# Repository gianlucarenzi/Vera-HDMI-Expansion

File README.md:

# VERA-HDMI-Expansion

<p align="center">
  An open-source HDMI expansion board for the <strong>VERA-MODULE-RBL</strong> video module.
</p>

---

## 📖 Overview

This project provides the complete design files for an HDMI expansion board specifically created for the **VERA-MODULE-RBL**. Its purpose is to convert the VERA module's native video signal into a standard HDMI output, allowing it to be easily connected to modern monitors and TVs.

The project was designed in KiCad, and all source files are included for viewing, modification, and manufacturing.

## ✨ Key Features

- 🔌 **Native HDMI Output:** Delivers a clean digital signal for maximum video quality.
- 🧩 **Compact Design:** Engineered to integrate seamlessly with the VERA-MODULE-RBL.
- ⚙️ **MS9288-Based:** Utilizes a dedicated chip for digital video to HDMI conversion.
- 📂 **Open Source:** All KiCad design files are freely available in this repository.

## 🛠️ How It Works

The board connects directly to the VERA-MODULE-RBL. The heart of the circuit is the **MS9288A/C** video converter chip, a specialized IC that receives digital video data from the VERA module, processes it, and encodes it into a TMDS (Transition-Minimized Differential Signaling) signal compatible with the HDMI standard.

This signal is then exposed via a standard HDMI connector, ready to be plugged into any modern display.

---

## 📚 Project Files & Documentation

### Schematic

The complete circuit schematic is available as a PDF for easy viewing.

- **[➡️ View Schematic (PDF)](VERA-HDMI-Expansion.pdf)**

### Bill of Materials (BOM)

An interactive HTML Bill of Materials (iBOM) is provided to simplify component identification and assembly.

- **[➡️ Open Interactive BOM](https://gianlucarenzi.github.io/Vera-HDMI-Expansion/BOM/ibom.html)**

### Mechanical Assembly

The board is mounted on the VERA-MODULE-RBL-XE with four 14 mm M3 standoffs and
eight M3x6 screws; J2 plugs into the J1 box header of the module.

- **[➡️ Mechanical BOM and stacking](Documentation/MECHANICAL-BOM.md)**
- 3D model of the stack: [`images/VERA-XE-HDMI-assembly.step`](images/VERA-XE-HDMI-assembly.step)

---

## 🏭 Manufacturing

This repository contains all the necessary files for board production, including:
- KiCad source files (`.kicad_pcb`, `.sch`).
- Python scripts (`generate_cpl.py`, `jlcpcb-check-bom.py`) to automate the generation of Component Placement Lists (CPL) and to verify the BOM against JLCPCB's library.
- Manufacturing outputs in the `production/` directory.

### Board Renders

<table align="center">
  <tr>
    <td align="center"><strong>Top View</strong></td>
    <td align="center"><strong>Bottom View</strong></td>
  </tr>
  <tr>
    <td></td>
    <td></td>
  </tr>
</table>

---

## 📜 License

This project is released under the terms specified in the [LICENSE](LICENSE) file.

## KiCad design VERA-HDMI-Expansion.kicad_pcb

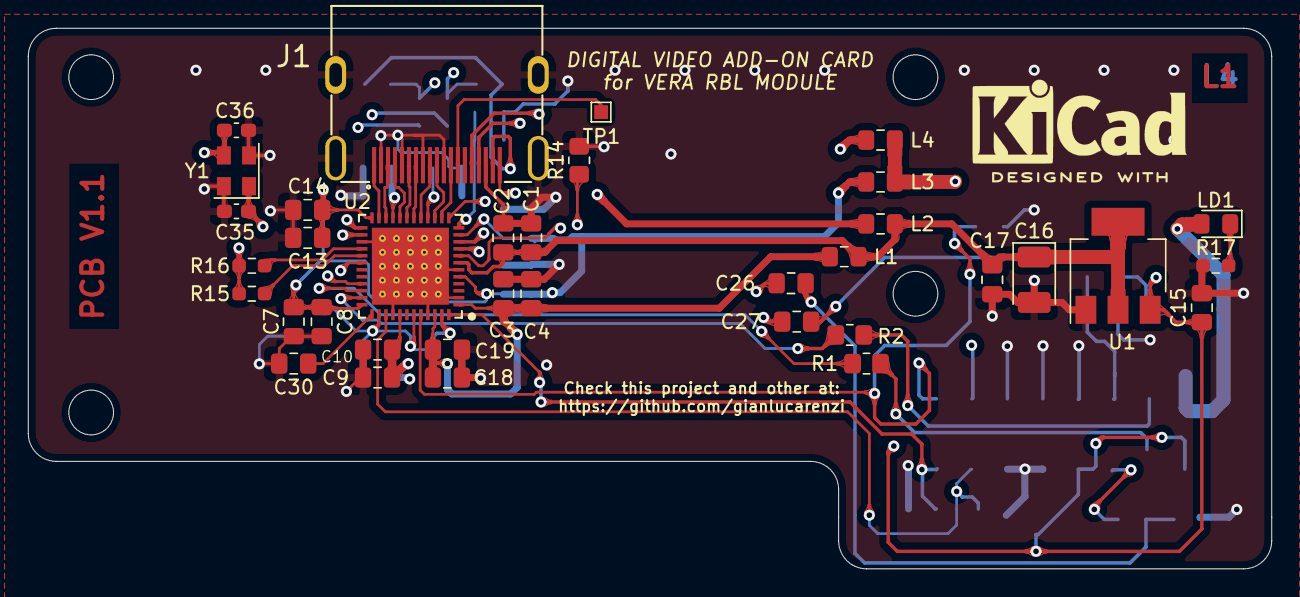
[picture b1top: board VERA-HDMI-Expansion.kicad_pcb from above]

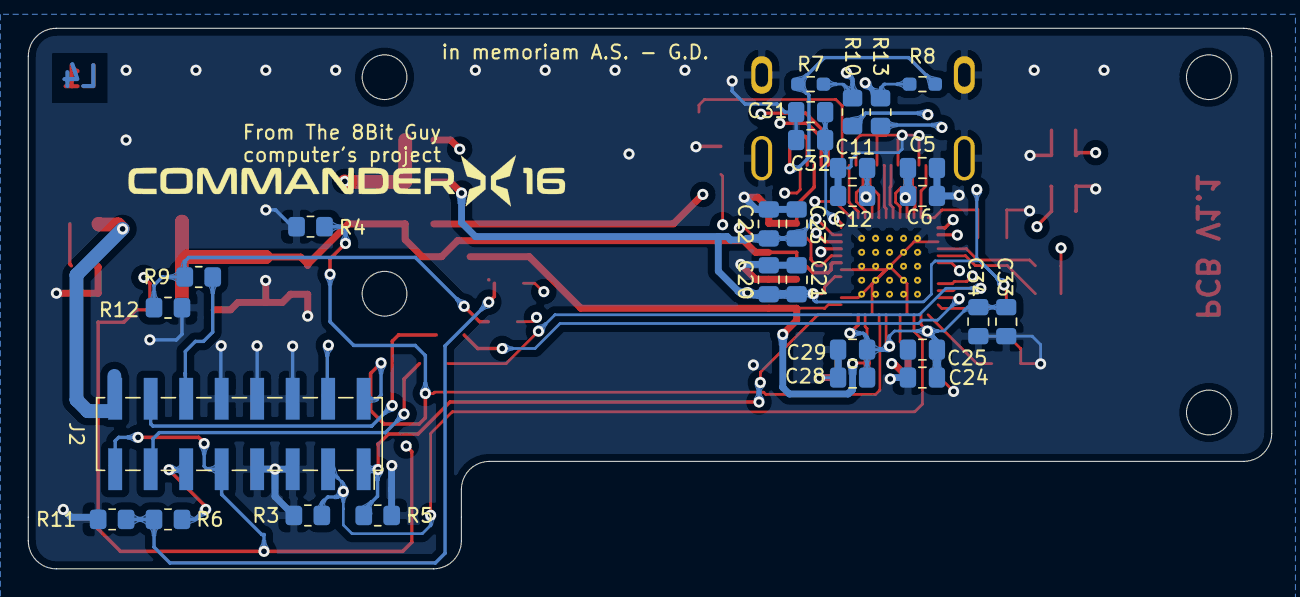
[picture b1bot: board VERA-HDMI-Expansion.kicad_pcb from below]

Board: 4 copper layers, 89.0 x 38.7 mm, 70 parts (29 on the bottom side), 42 nets.

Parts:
C1, C3, C5, C7, C9, C11, C13, C18, C20, C22, C24, C28, C31, C33: 22uF; C_0805_2012Metric_Pad1.18x1.45mm_HandSolder
C2, C4, C6, C8, C10, C12, C14, C15, C17, C19, C21, C23, C25, C29, C30, C32, C34: 100nF; C_0805_2012Metric_Pad1.18x1.45mm_HandSolder
C16: 10uF-20V; CP_EIA-3528-12_Kemet-T_Pad1.50x2.35mm_HandSolder
C26, C27: 470nF; C_0805_2012Metric_Pad1.18x1.45mm_HandSolder
C35, C36: 22pF; C_0603_1608Metric_Pad1.08x0.95mm_HandSolder
H1, H2, H3, H4: MountingHole; MountingHole_3.2mm_M3
J1: CONN_HDMI_A; CONN_HDMI-A
J2: CONN_SMD_02x08_Odd_Even_2.54mm; PinSocket_2x08_P2.54mm_Vertical_SMD_Bottom
L1, L2, L3, L4: FB080590R100MHZ850mA; L_0805_2012Metric_Pad1.15x1.40mm_HandSolder
LD1: GREEN; LED_0805_2012Metric_Pad1.15x1.40mm_HandSolder
LOGO1: KiCAD Logo; KiCad-Logo2_6mm_SilkScreen
LOGO2: Commander X16 Project; x16logo
R1, R2, R10, R13: 100R; R_0805_2012Metric_Pad1.20x1.40mm_HandSolder
R3, R4, R5: 75R; R_0805_2012Metric_Pad1.20x1.40mm_HandSolder
R6, R9, R11, R12: 10K; R_0805_2012Metric_Pad1.20x1.40mm_HandSolder
R7, R8, R15, R16: 2K7; R_0603_1608Metric_Pad0.98x0.95mm_HandSolder
R14: 1K; R_0805_2012Metric_Pad1.20x1.40mm_HandSolder
R17: 560R; R_0603_1608Metric_Pad0.98x0.95mm_HandSolder
TP1: TestPoint; TestPoint_Pad_1.0x1.0mm
U1: AMS1117-1.8; SOT-223-3_TabPin2
U2: MS9288C
Y1: 24.576Mhz; Crystal_SMD_EuroQuartz_MT-4Pin_3.2x2.5mm

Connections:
1V8: C1.1, C2.1, C16.1, C17.1, L1.1, L2.1, U1.2, U2.7
3V3: J2.4, J2.16, L3.1, L4.1, LD1.2, R15.1, R16.1
5V: C15.1, J1.18, J2.9, J2.15, R7.1, R8.1, U1.3
/AVDD18_0: C5.1, C6.1, C11.1, C12.1, L2.2, U2.16, U2.21
/AVDD18_ADC_0: C3.1, C4.1, C9.1, C10.1, C18.1, C19.1, L1.2, U2.1, U2.41, U2.46
/AVDD33_0: C24.1, C25.1, C28.1, C29.1, C31.1, C32.1, C33.1, C34.1, L4.2, U2.12, U2.38, U2.43, U2.47
/DDC_SCL: J1.15, R7.2, R10.1
/DDC_SDA: J1.16, R8.2, R13.1
/DVDD33_0: C7.1, C8.1, C13.1, C14.1, C20.1, C21.1, C22.1, C23.1, L3.2, U2.5, U2.11, U2.24, U2.36
/HDMI_TX0+: J1.7, U2.18
/HDMI_TX0-: J1.9, U2.17
/HDMI_TX1+: J1.4, U2.20
/HDMI_TX1-: J1.6, U2.19
/HDMI_TX2+: J1.1, U2.23
/HDMI_TX2-: J1.3, U2.22
/HDMI_TXC+: J1.10, U2.15
/HDMI_TXC-: J1.12, U2.14
AUDIOL: J2.11, R6.1
AUDIOR: J2.12, R9.1
GND: C1.2, C2.2, C3.2, C4.2, C5.2, C6.2, C7.2, C8.2, C9.2, C10.2, C11.2, C12.2, C13.2, C14.2, C15.2, C16.2, C17.2, C18.2, C19.2, C20.2, C21.2, C22.2, C23.2, C24.2, C25.2, C28.2, C29.2, C30.2, C31.2, C32.2, C33.2, C34.2, C35.1, C36.1, J1.2, J1.5, J1.8, J1.11, J1.17, J1.SH, J2.5, J2.6, J2.7, J2.8, J2.10, R3.1, R4.1, R5.1, R11.1, R12.1, R14.2, R17.2, U1.1, U2.2, U2.6, U2.27, U2.40, U2.45, U2.49, Y1.2, Y1.4
unnamed: C26.1, U2.30
unnamed: C26.2, R6.2, R11.2
unnamed: C27.1, U2.33
unnamed: C27.2, R9.2, R12.2
unnamed: C30.1, U2.37
unnamed: C35.2, U2.26, Y1.1
unnamed: C36.2, U2.25, Y1.3
unnamed: J1.13, TP1.1
unnamed: J1.19, U2.8
unnamed: LD1.1, R17.1
unnamed: R1.1, U2.34
unnamed: R2.1, U2.35
unnamed: R10.2, U2.10
unnamed: R13.2, U2.9
unnamed: R14.1, U2.13
unnamed: R15.2, U2.29
unnamed: R16.2, U2.28
VGABLUE: J2.3, R3.2, U2.39
VGAGREEN: J2.2, R4.2, U2.44
VGAHSYNC: J2.13, R1.2
VGARED: J2.1, R5.2, U2.48
VGAVSYNC: J2.14, R2.2

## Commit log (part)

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2025-10-17 Ignored fp-info-cache
2025-10-17 Added
2025-10-17 Updated messages
2025-10-17 Automate scripts
2025-10-17 Autogenerated
2025-10-23 Removed H2 Mounting Hole. PCB is bigger to accomodate the new position of H1 (16mm x 96mm from the right side of the bottom board)
2025-10-23 Automatically generate the PDF from schematics.
2025-10-29 Removed. Not needed now
2025-10-29 Added from the VERA-MODULE-RBL-XE project
2025-10-29 Ignore the cache.lib file
2025-10-29 Configuration for IBOM
2025-10-29 New pos file
2025-10-29 Autogenerated v1.1
2025-10-29 Updated & Autogenerated v1.1
2025-10-29 Python3 path for system XSLTPROC path for system
2025-10-29 Providing the kicad-cli shell script for Flatpak KiCAD 7+ version. Put the script into a reachable folder in PATH for the shell.
2025-10-29 Python3 path for system
2025-10-29 Autogenerated v1.1+
2025-10-29 Added more artifact to be ignored
2025-10-29 Removed (now the project does not include 'XE' string)
2025-10-29 Now the project does not include 'XE' string
2025-10-29 To be checked
2025-10-29 Added (now the project does not include 'XE' string)
2025-10-29 Renamed
2025-10-29 New date
2025-10-29 Removed. Must be launched from PCBNEW when ready for production. After the output_job.sh should be launched.
2025-10-29 Saved after a production plot run
2025-10-29 Ignored. The Gerbers must be created into PCBNEW, and then launched the output_job.sh script
2025-10-29 Ignore the autogenerated files from output_job.sh
2025-10-29 Updated for iBOM
2025-10-29 Ignored the compiled executables
2025-10-29 ignored the eeplot utilities
2025-10-29 Now it uses eeplot for plotting the PDF
2025-10-29 Autogenerated with eeplot
2025-10-29 24.576Mhz Crystal Oscillator added
2025-11-01 RetroBitLab library
